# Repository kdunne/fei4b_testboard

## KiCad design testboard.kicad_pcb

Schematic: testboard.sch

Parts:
C1, C2, C3, C4, C5, C6, C7, C8, C9, C10, C11, C12: C; C_0603
J1, J2, J3, J4: RJ45; RJ45_8
J5, J7, J8: Connector_Conn; conn
J6: LEMO2; lemo_epb00250ntn
M1: molex
U1: TTC_header; ttc_header
U2, U3, U5, U6: data_header
U4: header
U7, U8: Solder_Pad; Power_Pad
U9, U10, U11, U12, U13, U14, U15, U16, U17, U18, U19, U20, U21, U22, U23, U24, U25, U26, U27, U28, U29, U30, U31, U32, U33, U34, U35, U36, U37, U38, U39, U40: term

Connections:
/A_N: C5.1, C5.2, J1.8, J5.33, U2.1 (DO_P)
/A_N_conn: J7.33, U9.1
/A_N_conn1: J8.33, U25.1
/A_P: C6.1, C6.2, J1.7, J5.32, U2.2 (DO_N)
/A_P_conn: J7.32, U20.1
/A_P_conn1: J8.32, U33.1
/B_N: C7.1, C7.2, J3.8, J5.29, U3.1 (DO_P)
/B_N_conn: J7.29, U10.1
/B_N_conn1: J8.29, U26.1
/B_P: C8.1, C8.2, J3.7, J5.30, U3.2 (DO_N)
/B_P_conn: J7.30, U21.1
/B_P_conn1: J8.30, U34.1
/C_N: C9.1, C9.2, J2.8, J5.10, U5.1 (DO_P)
/C_N_conn: J7.10, U17.1
/C_N_conn1: J8.10, U38.1
/C_P: C10.1, C10.2, J2.7, J5.11, U5.2 (DO_N)
/C_P_conn: J7.11, U14.1
/C_P_conn1: J8.11, U30.1
/Clk_N: C1.1, C1.2, J1.2, J5.19, U1.1 (Clk_N)
/Clk_N_conn: J7.19, U12.1
/Clk_N_conn1: J8.19, U28.1
/Clk_P: C2.1, C2.2, J1.1, J5.20, U1.2 (Clk_P)
/Clk_P_conn: J7.20, U23.1
/Clk_P_conn1: J8.20, U36.1
/Cmd_N: C3.1, C3.2, J1.5, J5.23, U1.4 (Cmd_N)
/Cmd_N_conn: J7.23, U11.1
/Cmd_N_conn1: J8.23, U27.1
/Cmd_P: C4.1, C4.2, J1.4, J5.22, U1.5 (Cmd_P)
/Cmd_P_conn: J7.22, U22.1
/Cmd_P_conn1: J8.22, U35.1
/D_N: C11.1, C11.2, J4.8, J5.8, U6.1 (DO_P)
/D_N_conn: J7.8, U18.1
/D_N_conn1: J8.8, U39.1
/D_P: C12.1, C12.2, J4.7, J5.7, U6.2 (DO_N)
/D_P_conn: J7.7, U15.1
/D_P_conn1: J8.7, U31.1
/HV: J5.1, J6.1
/HV_Ret: J5.4, J6.2
/HV_Ret_conn: J7.4, U19.1
/HV_Ret_conn1: J8.4, U40.1
/HV_conn: J7.1, U16.1
/HV_conn1: J8.1, U32.1
/NTC: J1.3, J5.18, U1.3 (NTC)
/NTC_Ret: J1.6, J5.17, U1.6 (NTC_Ret)
/NTC_Ret_conn: J7.17, U13.1
/NTC_Ret_conn1: J8.17, U29.1
/NTC_conn: J7.18, U24.1
/NTC_conn1: J8.18, U37.1
/VDA_A: J5.24, U4.2 (VDA_A)
/VDA_B: J5.25, U4.4 (VDA_B)
/VDA_C: J5.14, U4.6 (VDA_C)
/VDA_D: J5.15, U4.8 (VDA_D)
/VDD_A: J5.26, U4.1 (VDD_A)
/VDD_B: J5.27, U4.3 (VDD_B)
/VDD_C: J5.16, U4.5 (VDD_C)
/VDD_D: J5.13, U4.7 (VDD_D)
/Vin: M1.1, M1.2, U4.21 (GND), U4.22 (GND), U4.23 (GND), U4.24 (GND), U8.1, U8.2
/Vin_A: J5.28, U4.9 (Vin_A)
/Vin_B: J5.31, U4.10 (Vin_B)
/Vin_C: J5.12, U4.11 (Vin_C)
/Vin_D: J5.9, U4.12 (Vin_D)
GND: M1.3, M1.4, U4.13 (GND), U4.14 (GND), U4.15 (GND), U4.16 (GND), U4.17 (GND), U4.18 (GND), U4.19 (GND), U4.20 (GND), U7.1, U7.2

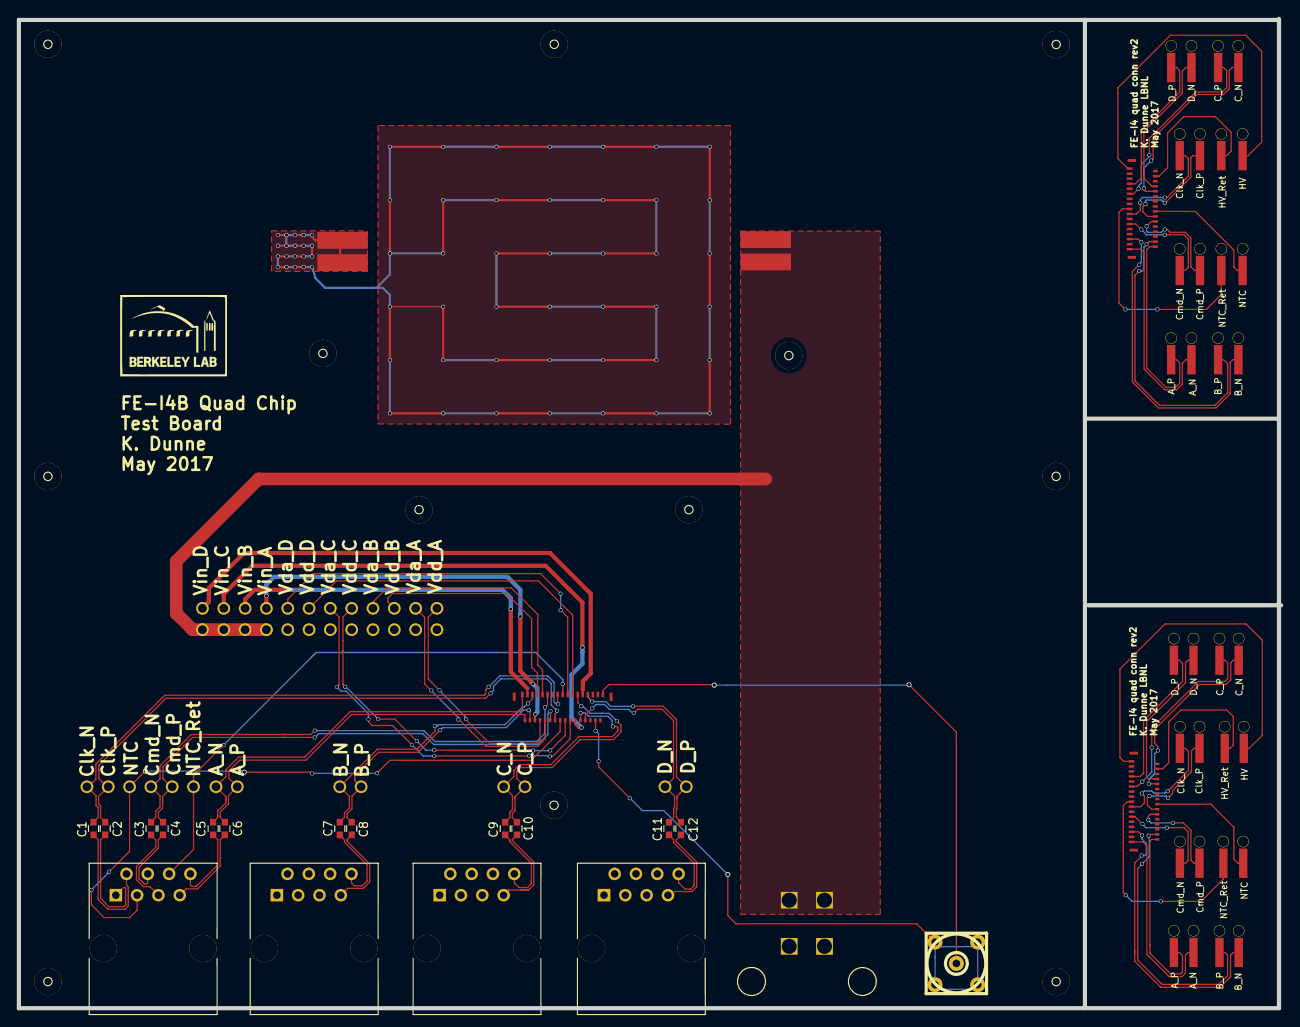
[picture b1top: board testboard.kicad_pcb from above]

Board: 2 copper layers, 150.1 x 117.9 mm, 61 parts (0 on the bottom side), 62 nets.

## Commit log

2017-08-18 Initialize repository
2017-10-05 Final version
